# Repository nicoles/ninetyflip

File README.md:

# ninetyflip
 
a lot of keys. so many keys. the numpad isn't where you'd expect.

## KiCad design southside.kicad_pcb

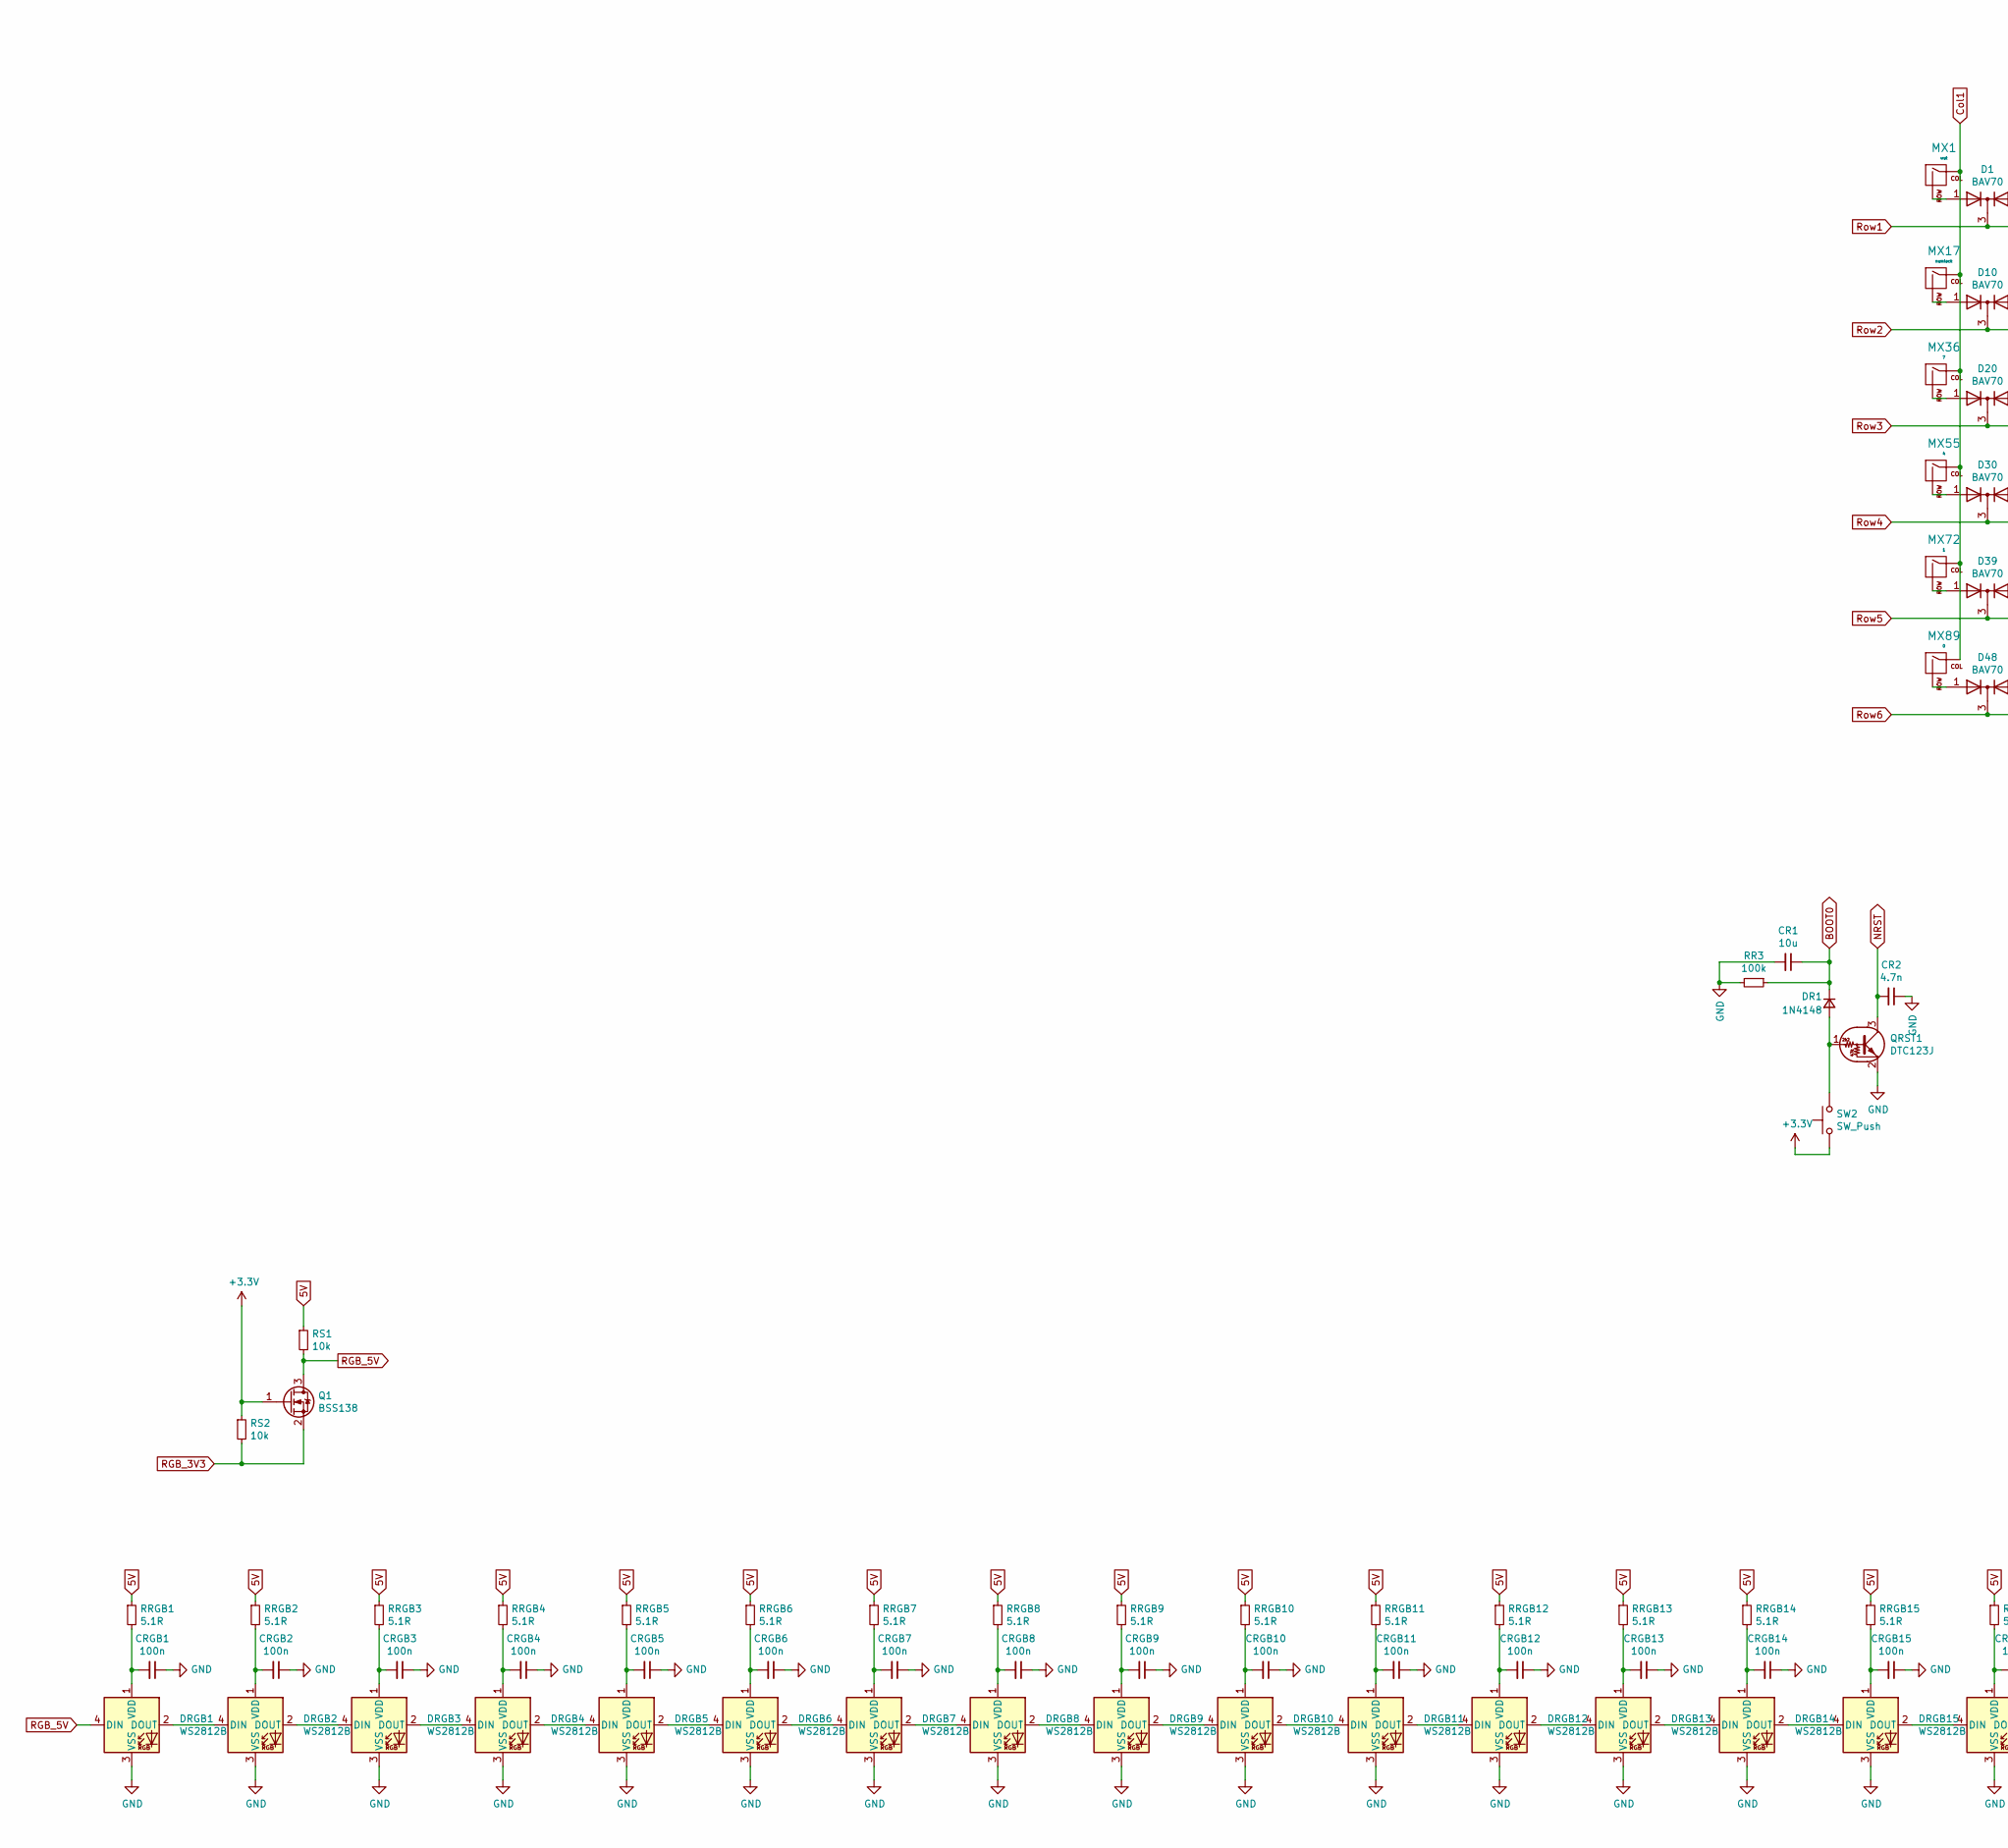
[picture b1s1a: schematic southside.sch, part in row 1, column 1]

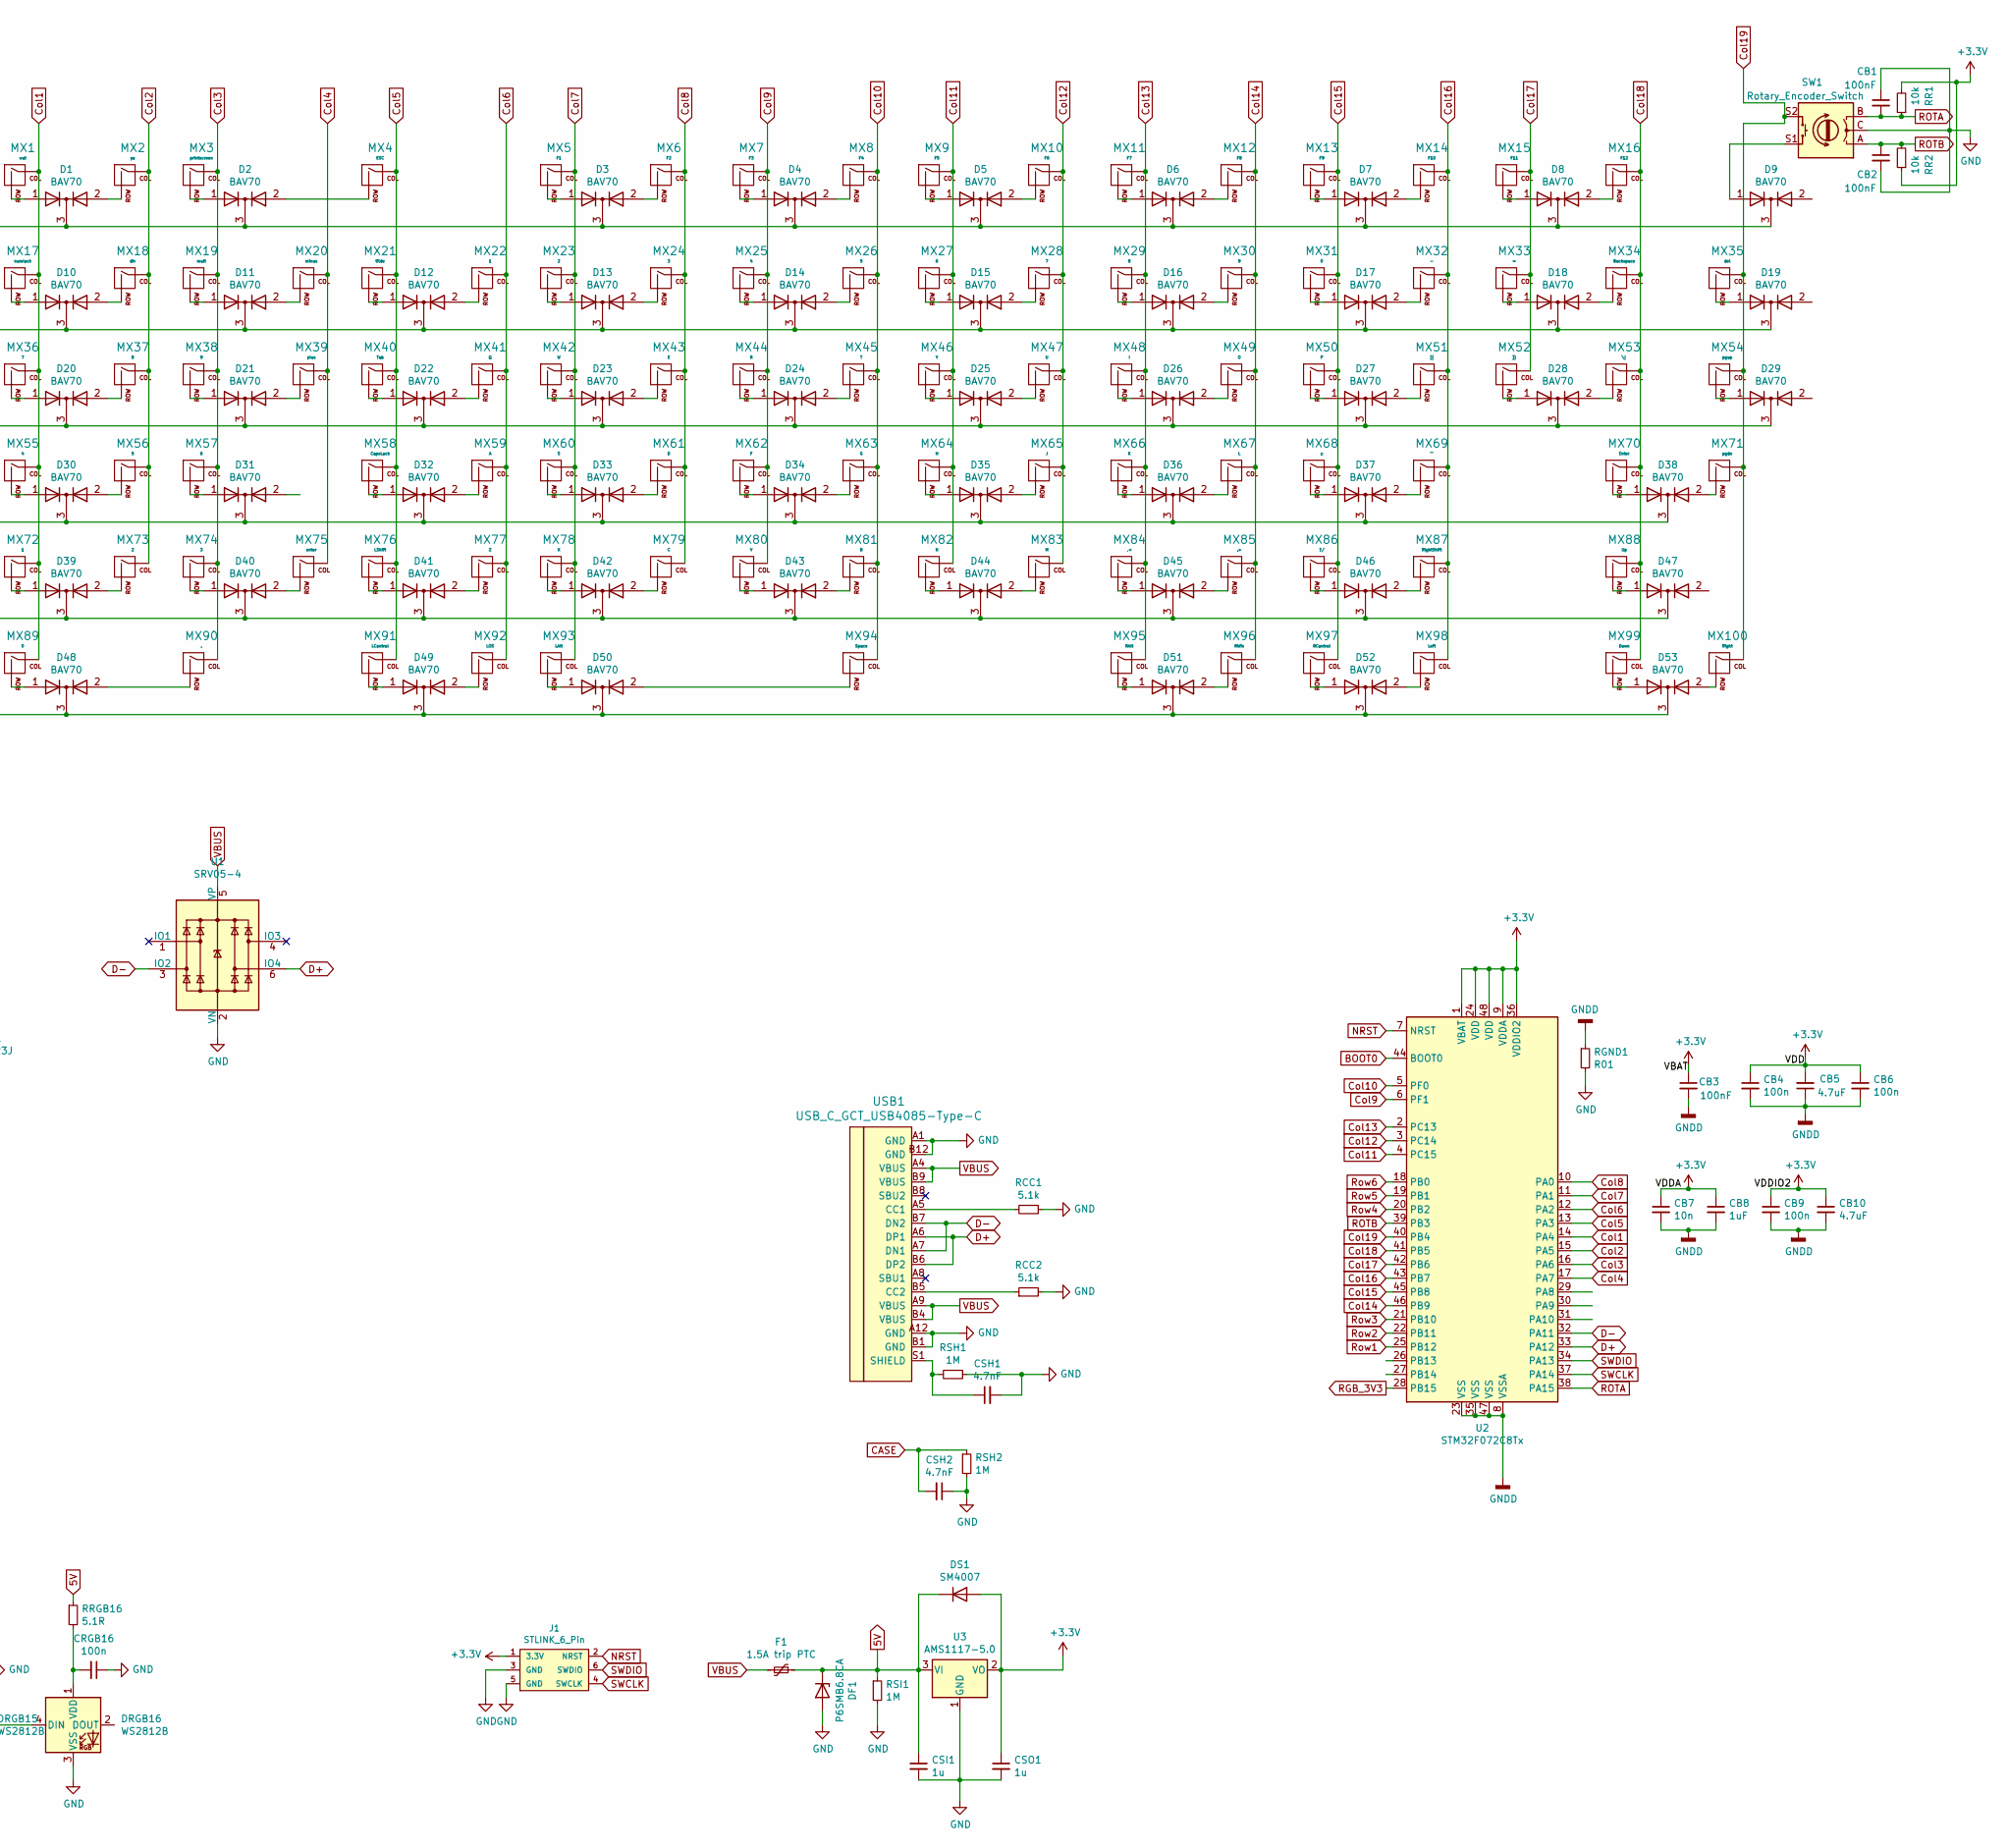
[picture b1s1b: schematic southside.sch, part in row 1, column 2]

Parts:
CB1, CB2, CB3: 100nF; C_0402_1005Metric; JLCCode C1525
CB4, CB6, CB9: 100n; C_0402_1005Metric; JLCCode C1525
CB5, CB10: 4.7uF; C_0402_1005Metric; JLCCode C23733
CB7: 10n; C_0402_1005Metric; JLCCode C15195
CB8: 1uF; C_0402_1005Metric; JLCCode C52923
CR1: 10u; C_0805_2012Metric; JLCCode C15850
CR2: 4.7n; C_0805_2012Metric; JLCCode C1744
CRGB1, CRGB2, CRGB3, CRGB4, CRGB5, CRGB6, CRGB7, CRGB8, CRGB9, CRGB10, CRGB11, CRGB12, CRGB13, CRGB14, CRGB15, CRGB16: 100n; C_0805_2012Metric
CSH1, CSH2: 4.7nF; C_0805_2012Metric; JLCCode C1744
CSI1: 1u; C_0805_2012Metric; JLCCode C28323
CSO1: 1u; C_0805_2012Metric; JLCCode C28323
D1, D2, D3, D4, D5, D6, D7, D8, D9, D10, D11, D12, D13, D14, D15, D16, D17, D18, D19, D20, D21, D22, D23, D24, D25, D26, D27, D28, D29, D30, D31, D32, D33, D34, D35, D36, D37, D38, D39, D40, D41, D42, D43, D44, D45, D46, D47, D48, D49, D50, D51, D52, D53: BAV70; SOT-23; JLCCode C68978
DF1: P6SMB6.8CA; D_SMB; JLCCode C78395
DR1: 1N4148; D_SOD-123; JLCCode C81598
DRGB1, DRGB2, DRGB3, DRGB4, DRGB5, DRGB6, DRGB7, DRGB8, DRGB9, DRGB10, DRGB11, DRGB12, DRGB13, DRGB14, DRGB15, DRGB16: WS2812B; LED_WS2812B_PLCC4_5.0x5.0mm_P3.2mm; JLCCode C114586
DS1: SM4007; D_SOD-123F; JLCCode C64898
F1: 1.5A trip PTC; Fuse_1812_4532Metric; JLCCode C84140
J1: STLINK_6_Pin; 2X3_LOCK
MX1: wut; MXOnly-1U-NoLED
MX2: yo; MXOnly-1U-NoLED
MX3: printscreen; MXOnly-1U-NoLED
MX4: ESC; MXOnly-1U-NoLED
MX5: F1; MXOnly-1U-NoLED
MX6: F2; MXOnly-1U-NoLED
MX7: F3; MXOnly-1U-NoLED
MX8: F4; MXOnly-1U-NoLED
MX9: F5; MXOnly-1U-NoLED
MX10: F6; MXOnly-1U-NoLED
MX11: F7; MXOnly-1U-NoLED
MX12: F8; MXOnly-1U-NoLED
MX13: F9; MXOnly-1U-NoLED
MX14: F10; MXOnly-1U-NoLED
MX15: F11; MXOnly-1U-NoLED
MX16: F12; MXOnly-1U-NoLED
MX17: numlock; MXOnly-1U-NoLED
MX18: div; MXOnly-1U-NoLED
MX19: mult; MXOnly-1U-NoLED
MX20: minus; MXOnly-1U-NoLED
MX21: tilde; MXOnly-1U-NoLED
MX22, MX72: 1; MXOnly-1U-NoLED
MX23, MX73: 2; MXOnly-1U-NoLED
MX24, MX74: 3; MXOnly-1U-NoLED
MX25, MX55: 4; MXOnly-1U-NoLED
MX26, MX56: 5; MXOnly-1U-NoLED
MX27, MX57: 6; MXOnly-1U-NoLED
MX28, MX36: 7; MXOnly-1U-NoLED
MX29, MX37: 8; MXOnly-1U-NoLED
MX30, MX38: 9; MXOnly-1U-NoLED
MX31: 0; MXOnly-1U-NoLED
MX32: -; MXOnly-1U-NoLED
MX33: =; MXOnly-1U-NoLED
MX34: Backspace; MXOnly-2U-NoLED
MX35: del; MXOnly-1U-NoLED
MX39: plus; MXOnly-2U-NoLED
MX40: Tab; MXOnly-1.5U-NoLED
MX41: Q; MXOnly-1U-NoLED
MX42: W; MXOnly-1U-NoLED
MX43: E; MXOnly-1U-NoLED
MX44: R; MXOnly-1U-NoLED
MX45: T; MXOnly-1U-NoLED
MX46: Y; MXOnly-1U-NoLED
MX47: U; MXOnly-1U-NoLED
MX48: I; MXOnly-1U-NoLED
MX49: O; MXOnly-1U-NoLED
MX50: P; MXOnly-1U-NoLED
MX51: [{; MXOnly-1U-NoLED
MX52: ]}; MXOnly-1U-NoLED
MX53: \\|; MXOnly-1.5U-NoLED
MX54: pgup; MXOnly-1U-NoLED
MX58: CapsLock; MXOnly-1.75U-NoLED
MX59: A; MXOnly-1U-NoLED
MX60: S; MXOnly-1U-NoLED
MX61: D; MXOnly-1U-NoLED
MX62: F; MXOnly-1U-NoLED
MX63: G; MXOnly-1U-NoLED
MX64: H; MXOnly-1U-NoLED
MX65: J; MXOnly-1U-NoLED
MX66: K; MXOnly-1U-NoLED
MX67: L; MXOnly-1U-NoLED
MX68: :;; MXOnly-1U-NoLED
MX69: \"'; MXOnly-1U-NoLED
MX70: Enter; MXOnly-2.25U-NoLED
MX71: pgdn; MXOnly-1U-NoLED
MX75: enter; MXOnly-2U-NoLED
MX76: LShift; MXOnly-2.25U-NoLED
MX77: Z; MXOnly-1U-NoLED
MX78: X; MXOnly-1U-NoLED
MX79: C; MXOnly-1U-NoLED
MX80: V; MXOnly-1U-NoLED
MX81: B; MXOnly-1U-NoLED
MX82: N; MXOnly-1U-NoLED
MX83: M; MXOnly-1U-NoLED
MX84: ,<; MXOnly-1U-NoLED
MX85: .>; MXOnly-1U-NoLED
MX86: ?/; MXOnly-1U-NoLED
MX87: RightShift; MXOnly-1.75U-NoLED
MX88: Up; MXOnly-1U-NoLED
MX89: 0; MXOnly-2U-ReversedStabilizers-NoLED
MX90: .; MXOnly-1U-NoLED
MX91: LControl; MXOnly-1.25U-NoLED
MX92: LOS; MXOnly-1.25U-NoLED
MX93: LAlt; MXOnly-1.25U-NoLED
MX94: Space; MXOnly-6.25U-ReversedStabilizers-NoLED
MX95: RAlt; MXOnly-1U-NoLED
MX96: RWin; MXOnly-1U-NoLED
MX97: RControl; MXOnly-1U-NoLED
MX98: Left; MXOnly-1U-NoLED
MX99: Down; MXOnly-1U-NoLED
MX100: Right; MXOnly-1U-NoLED
Q1: BSS138; SOT-23; JLCCode C193019
QRST1: DTC123J; SOT-23; JLCCode C111724
RCC1, RCC2: 5.1k; R_0805_2012Metric; JLCCode C27834
RGND1: R01; R_1206_3216Metric; JLCCode C127703
RR1, RR2: 10k; R_0402_1005Metric; JLCCode C25744
RR3: 100k; R_1206_3216Metric; JLCCode C17900
RRGB1, RRGB2, RRGB3, RRGB4, RRGB5, RRGB6, RRGB7, RRGB8, RRGB9, RRGB10, RRGB11, RRGB12, RRGB13, RRGB14, RRGB15, RRGB16: 5.1R; R_0805_2012Metric; JLCCode C17724
RS1, RS2: 10k; R_1206_3216Metric; JLCCode C17902
RSH1, RSH2: 1M; R_0805_2012Metric; JLCCode C17514
RSI1: 1M; R_0805_2012Metric; JLCCode C17514
SW1: Rotary_Encoder_Switch; RotaryEncoder_Alps_EC11E_Vertical_H20mm
SW2: SW_Push; smdPushBtn; JLCCode C318884
U1: SRV05-4; SOT-23-6; JLCCode C85364
U2: STM32F072C8Tx; LQFP-48_7x7mm_P0.5mm; JLCCode C80488
U3: AMS1117-5.0; SOT-223-3_TabPin2; JLCCode C6187
USB1: USB_C_GCT_USB4085-Type-C; USB_C_Receptacle_GCT_USB4085

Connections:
5V: CSI1.1, DF1.1 (K), DS1.1 (K), F1.1, RRGB1.1, RRGB2.1, RRGB3.1, RRGB4.1, RRGB5.1, RRGB6.1, RRGB7.1, RRGB8.1, RRGB9.1, RRGB10.1, RRGB11.1, RRGB12.1, RRGB13.1, RRGB14.1, RRGB15.1, RRGB16.1, RS1.1, RSI1.1, U3.3 (VI)
+3V3: CB3.1, CB4.1, CB5.2, CB6.1, CB7.1, CB8.1, CB9.1, CB10.1, CSO1.1, DS1.2 (A), J1.1 (3.3V), Q1.1 (G), RR1.2, RR2.1, RS2.1, SW2.1, U2.1 (VBAT), U2.9 (VDDA), U2.24 (VDD), U2.36 (VDDIO2), U2.48 (VDD), U3.2 (VO)
BOOT0: CR1.1, DR1.1 (K), RR3.1, U2.44 (BOOT0)
CASE: CSH2.2, RSH2.1
Col1: MX1.1 (COL), MX17.1 (COL), MX36.1 (COL), MX55.1 (COL), MX72.1 (COL), MX89.1 (COL), U2.14 (PA4)
Col2: MX2.1 (COL), MX18.1 (COL), MX37.1 (COL), MX56.1 (COL), MX73.1 (COL), U2.15 (PA5)
Col3: MX3.1 (COL), MX19.1 (COL), MX38.1 (COL), MX57.1 (COL), MX74.1 (COL), MX90.1 (COL), U2.16 (PA6)
Col4: MX20.1 (COL), MX39.1 (COL), MX75.1 (COL), U2.17 (PA7)
Col5: MX4.1 (COL), MX21.1 (COL), MX40.1 (COL), MX58.1 (COL), MX76.1 (COL), MX91.1 (COL), U2.13 (PA3)
Col6: MX22.1 (COL), MX41.1 (COL), MX59.1 (COL), MX77.1 (COL), MX92.1 (COL), U2.12 (PA2)
Col7: MX5.1 (COL), MX23.1 (COL), MX42.1 (COL), MX60.1 (COL), MX78.1 (COL), MX93.1 (COL), U2.11 (PA1)
Col8: MX6.1 (COL), MX24.1 (COL), MX43.1 (COL), MX61.1 (COL), MX79.1 (COL), U2.10 (PA0)
Col9: MX7.1 (COL), MX25.1 (COL), MX44.1 (COL), MX62.1 (COL), MX80.1 (COL), U2.6 (PF1)
Col10: MX8.1 (COL), MX26.1 (COL), MX45.1 (COL), MX63.1 (COL), MX81.1 (COL), MX94.1 (COL), U2.5 (PF0)
Col11: MX9.1 (COL), MX27.1 (COL), MX46.1 (COL), MX64.1 (COL), MX82.1 (COL), U2.4 (PC15)
Col12: MX10.1 (COL), MX28.1 (COL), MX47.1 (COL), MX65.1 (COL), MX83.1 (COL), U2.3 (PC14)
Col13: MX11.1 (COL), MX29.1 (COL), MX48.1 (COL), MX66.1 (COL), MX84.1 (COL), MX95.1 (COL), U2.2 (PC13)
Col14: MX12.1 (COL), MX30.1 (COL), MX49.1 (COL), MX67.1 (COL), MX85.1 (COL), MX96.1 (COL), U2.46 (PB9)
Col15: MX13.1 (COL), MX31.1 (COL), MX50.1 (COL), MX68.1 (COL), MX86.1 (COL), MX97.1 (COL), U2.45 (PB8)
Col16: MX14.1 (COL), MX32.1 (COL), MX51.1 (COL), MX69.1 (COL), MX87.1 (COL), MX98.1 (COL), U2.43 (PB7)
Col17: MX15.1 (COL), MX33.1 (COL), MX52.1 (COL), U2.42 (PB6)
Col18: MX16.1 (COL), MX34.1 (COL), MX53.1 (COL), MX70.1 (COL), MX88.1 (COL), MX99.1 (COL), U2.41 (PB5)
Col19: MX35.1 (COL), MX54.1 (COL), MX71.1 (COL), MX100.1 (COL), SW1.S2, U2.40 (PB4)
D+: U1.6 (IO4), U2.33 (PA12), USB1.A6 (DP1), USB1.B6 (DP2)
D-: U1.3 (IO2), U2.32 (PA11), USB1.A7 (DN1), USB1.B7 (DN2)
GND: CB1.1, CB2.2, CR1.2, CR2.1, CRGB1.1, CRGB2.1, CRGB3.1, CRGB4.1, CRGB5.1, CRGB6.1, CRGB7.1, CRGB8.1, CRGB9.1, CRGB10.1, CRGB11.1, CRGB12.1, CRGB13.1, CRGB14.1, CRGB15.1, CRGB16.1, CSH1.2, CSH2.1, CSI1.2, CSO1.2, DF1.2 (A), DRGB1.3 (VSS), DRGB2.3 (VSS), DRGB3.3 (VSS), DRGB4.3 (VSS), DRGB5.3 (VSS), DRGB6.3 (VSS), DRGB7.3 (VSS), DRGB8.3 (VSS), DRGB9.3 (VSS), DRGB10.3 (VSS), DRGB11.3 (VSS), DRGB12.3 (VSS), DRGB13.3 (VSS), DRGB14.3 (VSS), DRGB15.3 (VSS), DRGB16.3 (VSS), J1.3 (GND), J1.5 (GND), QRST1.2 (E), RCC1.1, RCC2.2, RGND1.2, RR3.2, RSH1.1, RSH2.2, RSI1.2, SW1.C, U1.2 (VN), U3.1 (GND), USB1.A1 (GND), USB1.A12 (GND), USB1.B1 (GND), USB1.B12 (GND)
GNDD: CB3.2, CB4.2, CB5.1, CB6.2, CB7.2, CB8.2, CB9.2, CB10.2, RGND1.1, U2.8 (VSSA), U2.23 (VSS), U2.35 (VSS), U2.47 (VSS)
NRST: CR2.2, J1.2 (NRST), QRST1.3 (C), U2.7 (NRST)
unnamed: CRGB1.2, DRGB1.1 (VDD), RRGB1.2
unnamed: CRGB2.2, DRGB2.1 (VDD), RRGB2.2
unnamed: CRGB3.2, DRGB3.1 (VDD), RRGB3.2
unnamed: CRGB4.2, DRGB4.1 (VDD), RRGB4.2
unnamed: CRGB5.2, DRGB5.1 (VDD), RRGB5.2
unnamed: CRGB6.2, DRGB6.1 (VDD), RRGB6.2
unnamed: CRGB7.2, DRGB7.1 (VDD), RRGB7.2
unnamed: CRGB8.2, DRGB8.1 (VDD), RRGB8.2
unnamed: CRGB9.2, DRGB9.1 (VDD), RRGB9.2
unnamed: CRGB10.2, DRGB10.1 (VDD), RRGB10.2
unnamed: CRGB11.2, DRGB11.1 (VDD), RRGB11.2
unnamed: CRGB12.2, DRGB12.1 (VDD), RRGB12.2
unnamed: CRGB13.2, DRGB13.1 (VDD), RRGB13.2
unnamed: CRGB14.2, DRGB14.1 (VDD), RRGB14.2
unnamed: CRGB15.2, DRGB15.1 (VDD), RRGB15.2
unnamed: CRGB16.2, DRGB16.1 (VDD), RRGB16.2
unnamed: CSH1.1, RSH1.2, USB1.S1 (SHIELD)
unnamed: D1.1 (A), MX1.2 (ROW)
unnamed: D1.2 (A), MX2.2 (ROW)
unnamed: D2.1 (A), MX3.2 (ROW)
unnamed: D2.2 (A), MX4.2 (ROW)
unnamed: D3.1 (A), MX5.2 (ROW)
unnamed: D3.2 (A), MX6.2 (ROW)
unnamed: D4.1 (A), MX7.2 (ROW)
unnamed: D4.2 (A), MX8.2 (ROW)
unnamed: D5.1 (A), MX9.2 (ROW)
unnamed: D5.2 (A), MX10.2 (ROW)
unnamed: D6.1 (A), MX11.2 (ROW)
unnamed: D6.2 (A), MX12.2 (ROW)
unnamed: D7.1 (A), MX13.2 (ROW)
unnamed: D7.2 (A), MX14.2 (ROW)
unnamed: D8.1 (A), MX15.2 (ROW)
unnamed: D8.2 (A), MX16.2 (ROW)
unnamed: D9.1 (A), SW1.S1
unnamed: D10.1 (A), MX17.2 (ROW)
unnamed: D10.2 (A), MX18.2 (ROW)
unnamed: D11.1 (A), MX19.2 (ROW)
unnamed: D11.2 (A), MX20.2 (ROW)
unnamed: D12.1 (A), MX21.2 (ROW)
unnamed: D12.2 (A), MX22.2 (ROW)
unnamed: D13.1 (A), MX23.2 (ROW)
unnamed: D13.2 (A), MX24.2 (ROW)
unnamed: D14.1 (A), MX25.2 (ROW)
unnamed: D14.2 (A), MX26.2 (ROW)
unnamed: D15.1 (A), MX27.2 (ROW)
unnamed: D15.2 (A), MX28.2 (ROW)
unnamed: D16.1 (A), MX29.2 (ROW)
unnamed: D16.2 (A), MX30.2 (ROW)
unnamed: D17.1 (A), MX31.2 (ROW)
unnamed: D17.2 (A), MX32.2 (ROW)
unnamed: D18.1 (A), MX33.2 (ROW)
unnamed: D18.2 (A), MX34.2 (ROW)
unnamed: D19.1 (A), MX35.2 (ROW)
unnamed: D20.1 (A), MX36.2 (ROW)
unnamed: D20.2 (A), MX37.2 (ROW)
unnamed: D21.1 (A), MX38.2 (ROW)
unnamed: D21.2 (A), MX39.2 (ROW)
unnamed: D22.1 (A), MX40.2 (ROW)
unnamed: D22.2 (A), MX41.2 (ROW)
unnamed: D23.1 (A), MX42.2 (ROW)
unnamed: D23.2 (A), MX43.2 (ROW)
unnamed: D24.1 (A), MX44.2 (ROW)
unnamed: D24.2 (A), MX45.2 (ROW)
unnamed: D25.1 (A), MX46.2 (ROW)
unnamed: D25.2 (A), MX47.2 (ROW)
unnamed: D26.1 (A), MX48.2 (ROW)
unnamed: D26.2 (A), MX49.2 (ROW)
unnamed: D27.1 (A), MX50.2 (ROW)
unnamed: D27.2 (A), MX51.2 (ROW)
unnamed: D28.1 (A), MX52.2 (ROW)
unnamed: D28.2 (A), MX53.2 (ROW)
unnamed: D29.1 (A), MX54.2 (ROW)
unnamed: D30.1 (A), MX55.2 (ROW)
unnamed: D30.2 (A), MX56.2 (ROW)
unnamed: D31.1 (A), MX57.2 (ROW)
unnamed: D32.1 (A), MX58.2 (ROW)
unnamed: D32.2 (A), MX59.2 (ROW)
unnamed: D33.1 (A), MX60.2 (ROW)
unnamed: D33.2 (A), MX61.2 (ROW)
unnamed: D34.1 (A), MX62.2 (ROW)
unnamed: D34.2 (A), MX63.2 (ROW)
unnamed: D35.1 (A), MX64.2 (ROW)
unnamed: D35.2 (A), MX65.2 (ROW)
unnamed: D36.1 (A), MX66.2 (ROW)
unnamed: D36.2 (A), MX67.2 (ROW)
unnamed: D37.1 (A), MX68.2 (ROW)
unnamed: D37.2 (A), MX69.2 (ROW)
unnamed: D38.1 (A), MX70.2 (ROW)
unnamed: D38.2 (A), MX71.2 (ROW)
unnamed: D39.1 (A), MX72.2 (ROW)
unnamed: D39.2 (A), MX73.2 (ROW)
unnamed: D40.1 (A), MX74.2 (ROW)
unnamed: D40.2 (A), MX75.2 (ROW)
unnamed: D41.1 (A), MX76.2 (ROW)
unnamed: D41.2 (A), MX77.2 (ROW)
unnamed: D42.1 (A), MX78.2 (ROW)
unnamed: D42.2 (A), MX79.2 (ROW)
unnamed: D43.1 (A), MX80.2 (ROW)
unnamed: D43.2 (A), MX81.2 (ROW)
unnamed: D44.1 (A), MX82.2 (ROW)
unnamed: D44.2 (A), MX83.2 (ROW)
unnamed: D45.1 (A), MX84.2 (ROW)
unnamed: D45.2 (A), MX85.2 (ROW)
unnamed: D46.1 (A), MX86.2 (ROW)
unnamed: D46.2 (A), MX87.2 (ROW)
unnamed: D47.1 (A), MX88.2 (ROW)
unnamed: D48.1 (A), MX89.2 (ROW)
unnamed: D48.2 (A), MX90.2 (ROW)
unnamed: D49.1 (A), MX91.2 (ROW)
unnamed: D49.2 (A), MX92.2 (ROW)
unnamed: D50.1 (A), MX93.2 (ROW)
unnamed: D50.2 (A), MX94.2 (ROW)
unnamed: D51.1 (A), MX95.2 (ROW)
unnamed: D51.2 (A), MX96.2 (ROW)
unnamed: D52.1 (A), MX97.2 (ROW)
unnamed: D52.2 (A), MX98.2 (ROW)
unnamed: D53.1 (A), MX99.2 (ROW)
unnamed: D53.2 (A), MX100.2 (ROW)
unnamed: DR1.2 (A), QRST1.1 (B), SW2.2
unnamed: DRGB1.2 (DOUT), DRGB2.4 (DIN)
unnamed: DRGB2.2 (DOUT), DRGB3.4 (DIN)
unnamed: DRGB3.2 (DOUT), DRGB4.4 (DIN)
unnamed: DRGB4.2 (DOUT), DRGB5.4 (DIN)
unnamed: DRGB5.2 (DOUT), DRGB6.4 (DIN)
unnamed: DRGB6.2 (DOUT), DRGB7.4 (DIN)
unnamed: DRGB7.2 (DOUT), DRGB8.4 (DIN)
unnamed: DRGB8.2 (DOUT), DRGB9.4 (DIN)
unnamed: DRGB10.2 (DOUT), DRGB11.4 (DIN)
unnamed: DRGB9.2 (DOUT), DRGB10.4 (DIN)
unnamed: DRGB11.2 (DOUT), DRGB12.4 (DIN)
unnamed: DRGB12.2 (DOUT), DRGB13.4 (DIN)
unnamed: DRGB13.2 (DOUT), DRGB14.4 (DIN)
unnamed: DRGB14.2 (DOUT), DRGB15.4 (DIN)
unnamed: DRGB15.2 (DOUT), DRGB16.4 (DIN)
unnamed: RCC1.2, USB1.A5 (CC1)
unnamed: RCC2.1, USB1.B5 (CC2)
RGB_3V3: Q1.2 (S), RS2.2, U2.28 (PB15)
RGB_5V: DRGB1.4 (DIN), Q1.3 (D), RS1.2
ROTA: CB1.2, RR1.1, SW1.B, U2.38 (PA15)
ROTB: CB2.1, RR2.2, SW1.A, U2.39 (PB3)
Row1: D1.3 (K), D2.3 (K), D3.3 (K), D4.3 (K), D5.3 (K), D6.3 (K), D7.3 (K), D8.3 (K), D9.3 (K), U2.25 (PB12)
Row2: D10.3 (K), D11.3 (K), D12.3 (K), D13.3 (K), D14.3 (K), D15.3 (K), D16.3 (K), D17.3 (K), D18.3 (K), D19.3 (K), U2.22 (PB11)
Row3: D20.3 (K), D21.3 (K), D22.3 (K), D23.3 (K), D24.3 (K), D25.3 (K), D26.3 (K), D27.3 (K), D28.3 (K), D29.3 (K), U2.21 (PB10)
Row4: D30.3 (K), D31.3 (K), D32.3 (K), D33.3 (K), D34.3 (K), D35.3 (K), D36.3 (K), D37.3 (K), D38.3 (K), U2.20 (PB2)
Row5: D39.3 (K), D40.3 (K), D41.3 (K), D42.3 (K), D43.3 (K), D44.3 (K), D45.3 (K), D46.3 (K), D47.3 (K), U2.19 (PB1)
Row6: D48.3 (K), D49.3 (K), D50.3 (K), D51.3 (K), D52.3 (K), D53.3 (K), U2.18 (PB0)
SWCLK: J1.4 (SWCLK), U2.37 (PA14)
SWDIO: J1.6 (SWDIO), U2.34 (PA13)
VBUS: F1.2, U1.5 (VP), USB1.A4 (VBUS), USB1.A9 (VBUS), USB1.B4 (VBUS), USB1.B9 (VBUS)

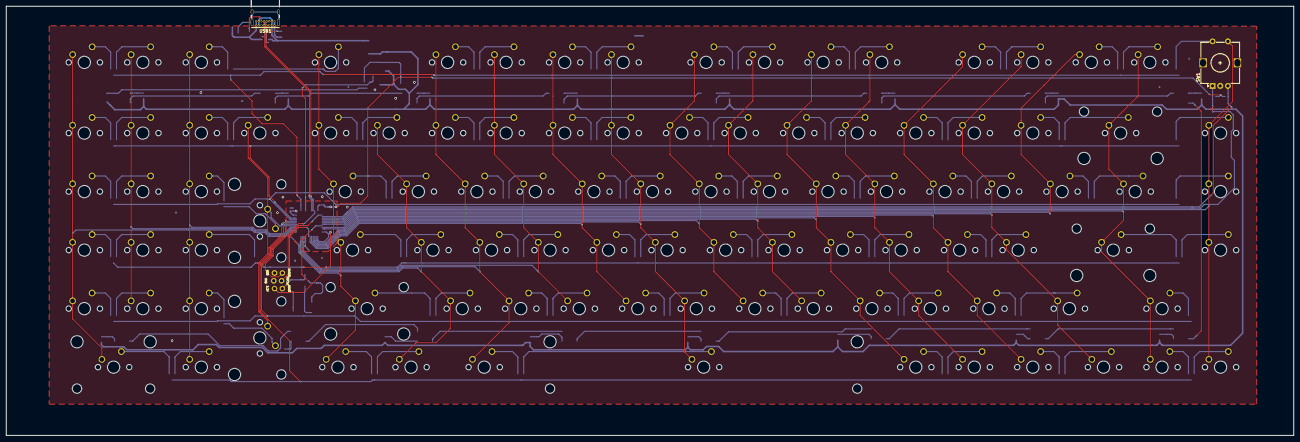
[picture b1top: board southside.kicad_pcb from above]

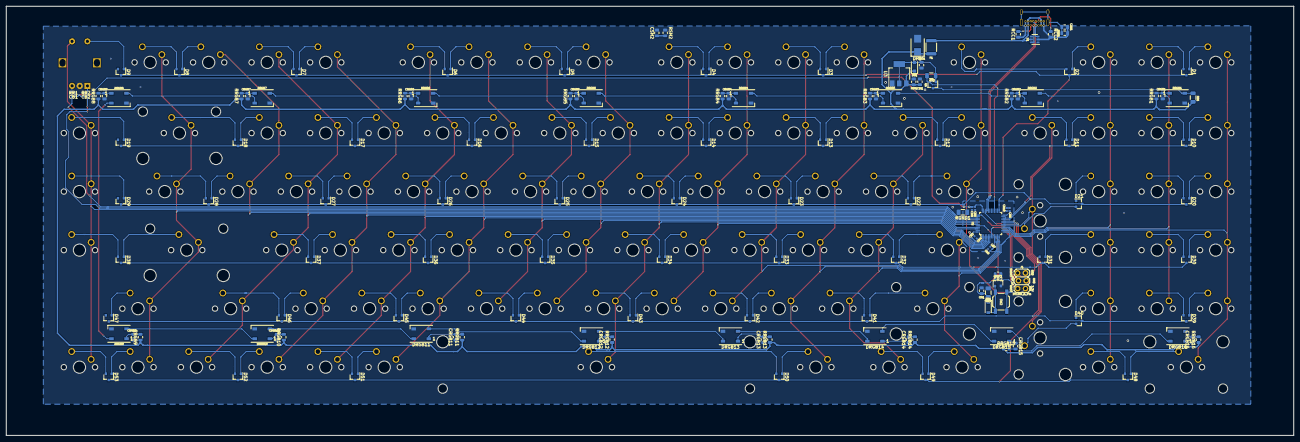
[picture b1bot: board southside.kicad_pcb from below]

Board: 2 copper layers, 419.1 x 139.7 mm, 241 parts (139 on the bottom side), 177 nets.

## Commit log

2020-08-31 Oops all changes
    yes'm, that's most of the board.
2020-09-02 now with more rotary
2020-10-07 bottom, top plate, many tweaks, some art
